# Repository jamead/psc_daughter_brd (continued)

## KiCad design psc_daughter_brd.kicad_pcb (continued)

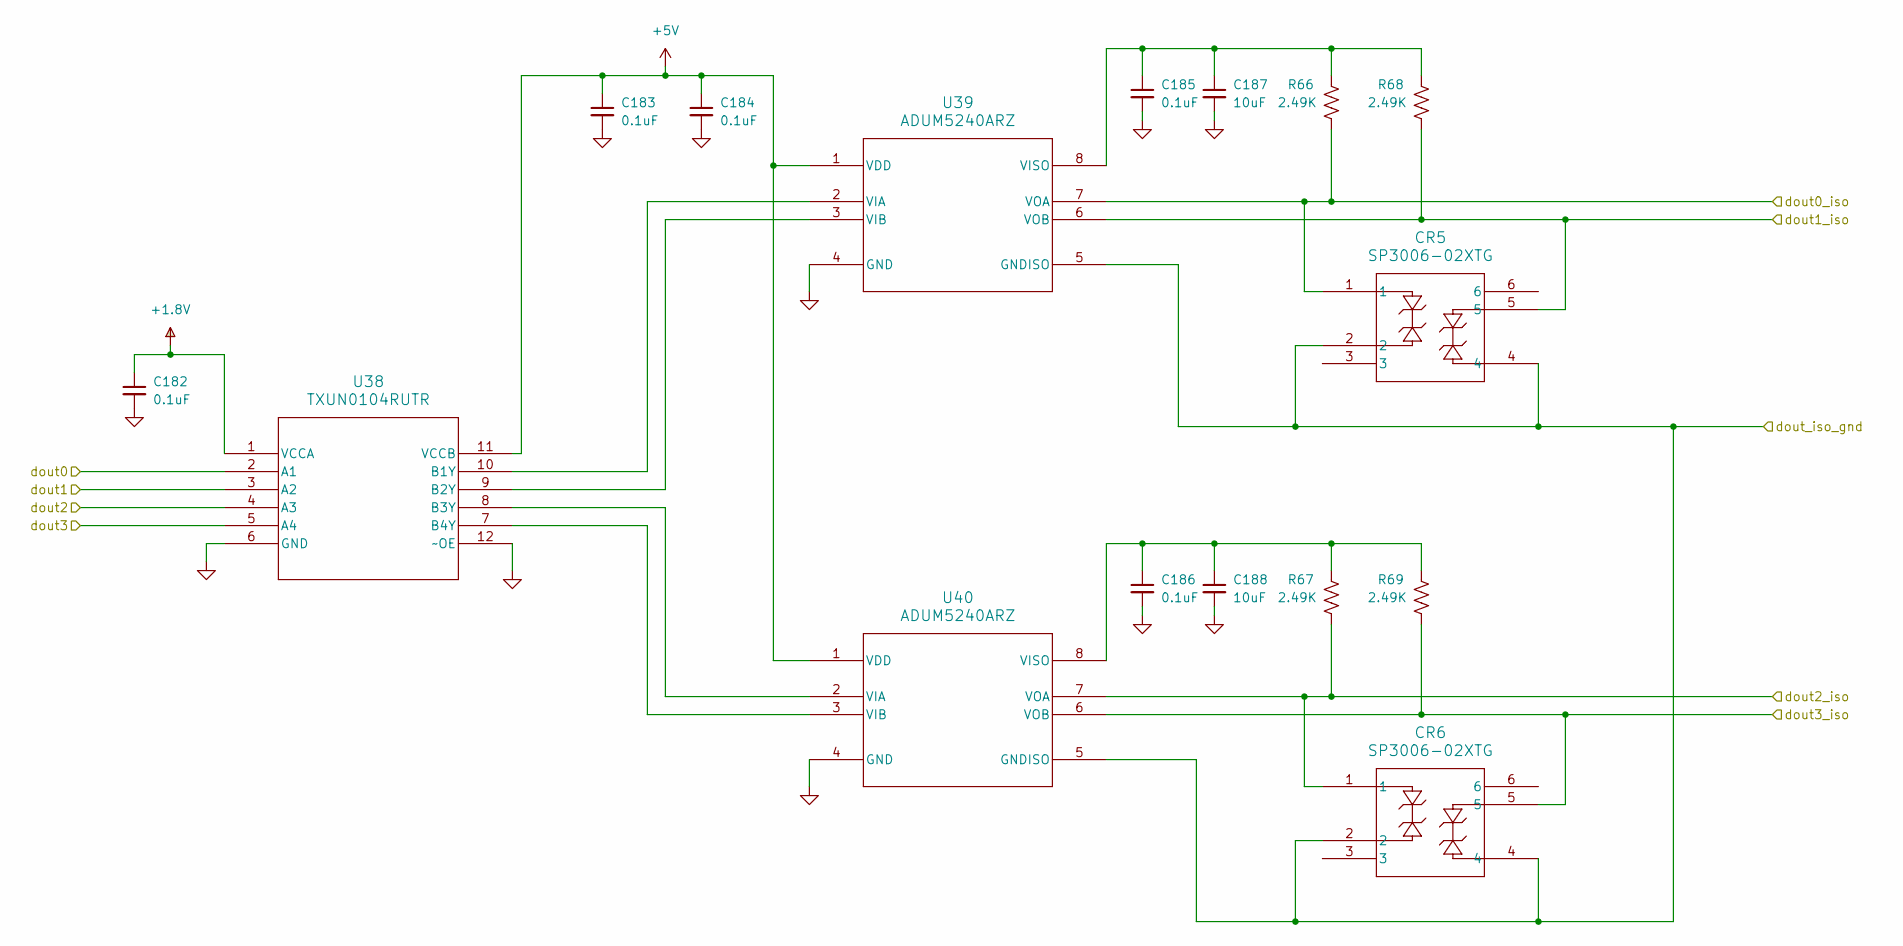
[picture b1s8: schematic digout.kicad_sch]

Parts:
C182, C183, C184, C185, C186: 0.1uF; C_0402_1005Metric
C187, C188: 10uF; C_0603_1608Metric; Voltage 25V
CR5, CR6: SP3006-02XTG; SOT563_LTF
R66, R67, R68, R69: 2.49K; R_0402_1005Metric; Tolerance 1%
U38: TXUN0104RUTR; PQFP12_RUT_TEX
U39, U40: ADUM5240ARZ; R_8_ADI

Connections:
+1.8V: C182.1, U38.1 (VCCA); also elsewhere on the board
+5V: C183.1, C184.1, U38.11 (VCCB), U39.1 (VDD), U40.1 (VDD); also elsewhere on the board
/FPGA connector/dout0: U38.2 (A1); also elsewhere on the board
/FPGA connector/dout1: U38.3 (A2); also elsewhere on the board
/FPGA connector/dout2: U38.4 (A3); also elsewhere on the board
/FPGA connector/dout3: U38.5 (A4); also elsewhere on the board
/Isolated Digital IO/dout0_iso: CR5.1, R66.1, U39.7 (VOA); also elsewhere on the board
/Isolated Digital IO/dout1_iso: CR5.5, R68.1, U39.6 (VOB); also elsewhere on the board
/Isolated Digital IO/dout2_iso: CR6.1, R67.1, U40.7 (VOA); also elsewhere on the board
/Isolated Digital IO/dout3_iso: CR6.5, R69.1, U40.6 (VOB); also elsewhere on the board
/Isolated Digital IO/dout_iso_gnd: CR5.2, CR5.4, CR6.2, CR6.4, U39.5 (GNDISO), U40.5 (GNDISO)
GND: C182.2, C183.2, C184.2, C185.2, C186.2, C187.2, C188.2, U38.6 (GND), U38.12 (~OE), U39.4 (GND), U40.4 (GND); also elsewhere on the board
unnamed: U38.10 (B1Y), U39.2 (VIA)
unnamed: U38.9 (B2Y), U39.3 (VIB)
unnamed: U38.8 (B3Y), U40.2 (VIA)
unnamed: U38.7 (B4Y), U40.3 (VIB)
unnamed: C185.1, C187.1, R66.2, R68.2, U39.8 (VISO)
unnamed: C186.1, C188.1, R67.2, R69.2, U40.8 (VISO)

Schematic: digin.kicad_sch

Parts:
C189, C190, C191, C192, C193: 0.1uF; C_0402_1005Metric
C194, C195: 10uF; C_0603_1608Metric; Voltage 25V
CR7, CR8: SP3006-02XTG; SOT563_LTF
R70, R71, R72, R73: 2.49K; R_0402_1005Metric; Tolerance 1%
U41: TXUN0104RUTR; PQFP12_RUT_TEX
U42, U43: ADUM5242ARZ; R_8_ADI

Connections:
+1V8: C189.1, U41.11 (VCCB)
+5V: C190.1, C191.1, U41.1 (VCCA), U42.1 (VDD), U43.1 (VDD); also elsewhere on the board
/FPGA connector/din0: U41.10 (B1Y); also elsewhere on the board
/FPGA connector/din1: U41.9 (B2Y); also elsewhere on the board
/FPGA connector/din2: U41.8 (B3Y); also elsewhere on the board
/FPGA connector/din3: U41.7 (B4Y); also elsewhere on the board
/Isolated Digital IO/din0_iso: CR7.1, R70.1, U42.7 (VIA); also elsewhere on the board
/Isolated Digital IO/din1_iso: CR7.5, R72.1, U42.6 (VIB); also elsewhere on the board
/Isolated Digital IO/din2_iso: CR8.1, R71.1, U43.7 (VIA); also elsewhere on the board
/Isolated Digital IO/din3_iso: CR8.5, R73.1, U43.6 (VIB); also elsewhere on the board
/Isolated Digital IO/din_iso_gnd: CR7.2, CR7.4, CR8.2, CR8.4, U42.5 (GNDISO), U43.5 (GNDISO)
GND: C189.2, C190.2, C191.2, C192.2, C193.2, C194.2, C195.2, U41.6 (GND), U41.12 (~OE), U42.4 (GND), U43.4 (GND); also elsewhere on the board
unnamed: U41.2 (A1), U42.2 (VOA)
unnamed: U41.3 (A2), U42.3 (VOB)
unnamed: U41.4 (A3), U43.2 (VOA)
unnamed: U41.5 (A4), U43.3 (VOB)
unnamed: C192.1, C194.1, R70.2, R72.2, U42.8 (VISO)
unnamed: C193.1, C195.1, R71.2, R73.2, U43.8 (VISO)

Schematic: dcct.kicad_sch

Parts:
C149, C150, C167, C169, C175, C177: 6800pF; C_0402_1005Metric
C151, C168, C176: 3300pF; C_0402_1005Metric
C152, C158, C163, C165, C173, C174, C179, C181: 0.1uF; C_0402_1005Metric
C154, C156, C161, C162, C171, C172, C178, C180: 10uF; C_0603_1608Metric; Voltage 25V
C159: 0.01uF; C_0402_1005Metric
R54, R55: 1.0K; R_0402_1005Metric; Tolerance 0.1%
R56: 665; R_0402_1005Metric; Tolerance 0.1%
R58: 1.3K; R_0402_1005Metric; Tolerance 1%
R62: 10; R_0402_1005Metric; Tolerance 0.1%
R63: 15; R_0402_1005Metric; Tolerance 0.1%
R64, R65: 30.1; R_0402_1005Metric; Tolerance 1%
U33: AD8429BRZ; SOIC127P600X175-8N
U34: AD8675ARZ; SOIC-8_3.9x4.9mm_P1.27mm
U36: LTC6363xMS8; MSOP-8_3x3mm_P0.65mm
U37: LTC2376CDE-20-PBF; DFN-16_DE_LIT

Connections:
+1.8V: C180.1, C181.1, U37.15 (OVDD); also elsewhere on the board
+2.5V: C178.1, C179.1, U37.2 (VDD); also elsewhere on the board
+5.3VA: C171.1, C173.1, U36.3 (V+); also elsewhere on the board
+15V: C156.1, C158.1, C162.1, C165.1, U33.8 (Vs+), U34.7 (V+); also elsewhere on the board
-5.3VA: C172.1, C174.1, U36.6 (V-); also elsewhere on the board
-15V: C152.1, C154.1, C161.1, C163.1, U33.5 (Vs-), U34.4 (V-); also elsewhere on the board
/DCCT ADCs/DCCT Channel 1/adc_vref: U37.7 (REF), U37.8 (REF/*DGC); also elsewhere on the board
/DCCT ADCs/DCCT Channel 1/drv_vref: U36.2 (VOCM); also elsewhere on the board
/DCCT ADCs/dcct0+: R55.2; also elsewhere on the board
/DCCT ADCs/dcct0-: R54.2; also elsewhere on the board
/DCCT ADCs/dcct0_sdo: U37.14 (SDO); also elsewhere on the board
/DCCT ADCs/dcct_busy: U37.11 (BUSY); also elsewhere on the board
/DCCT ADCs/dcct_cnv: U37.9 (CNV); also elsewhere on the board
/DCCT ADCs/dcct_sck: U37.13 (SCK); also elsewhere on the board
GND: C149.1, C150.2, C152.2, C154.2, C156.2, C158.2, C159.2, C161.2, C162.2, C163.2, C165.2, C167.1, C169.2, C171.2, C172.2, C173.2, C174.2, C175.1, C177.2, C178.2, C179.2, C180.2, C181.2, R63.2, U33.6 (Ref), U37.1 (CHAIN), U37.3 (GND), U37.6 (GND), U37.10 (GND), U37.12 (RDL/SDI), U37.16 (GND), U37.17 (GND); also elsewhere on the board
unnamed: C167.2, C168.1, R62.1, U36.8 (+)
unnamed: C168.2, C169.1, R63.1, U36.1 (-)
unnamed: R56.1, U33.2 (Rg)
unnamed: R56.2, U33.3 (Rg)
unnamed: R58.2, U33.7
unnamed: R64.2, U36.5 (-)
unnamed: R65.2, U36.4 (+)
unnamed: C150.1, C151.2, R55.1, U33.4 (+)
unnamed: C149.2, C151.1, R54.1, U33.1 (-)
unnamed: C159.1, R58.1, U34.3 (+)
unnamed: R62.2, U34.2 (-), U34.6
unnamed: C176.2, C177.1, R65.1, U37.4 (IN+)
unnamed: C175.2, C176.1, R64.1, U37.5 (IN-)

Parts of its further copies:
C114, C115, C132, C134, C140, C142: 6800pF; C_0402_1005Metric
C116, C133, C141: 3300pF; C_0402_1005Metric
C117, C123, C128, C130, C138, C139, C144, C146: 0.1uF; C_0402_1005Metric
C119, C121, C126, C127, C136, C137, C143, C145: 10uF; C_0603_1608Metric; Voltage 25V
C124: 0.01uF; C_0402_1005Metric
R42, R43: 1.0K; R_0402_1005Metric; Tolerance 0.1%
R44: 665; R_0402_1005Metric; Tolerance 0.1%
R46: 1.3K; R_0402_1005Metric; Tolerance 1%
R50: 10; R_0402_1005Metric; Tolerance 0.1%
R51: 15; R_0402_1005Metric; Tolerance 0.1%
R52, R53: 30.1; R_0402_1005Metric; Tolerance 1%
U27: AD8429BRZ; SOIC127P600X175-8N
U28: AD8675ARZ; SOIC-8_3.9x4.9mm_P1.27mm
U30: LTC6363xMS8; MSOP-8_3x3mm_P0.65mm
U31: LTC2376CDE-20-PBF; DFN-16_DE_LIT

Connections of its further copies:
+1.8V: C145.1, C146.1, U31.15 (OVDD); also elsewhere on the board
+2.5V: C143.1, C144.1, U31.2 (VDD); also elsewhere on the board
+5.3VA: C136.1, C138.1, U30.3 (V+); also elsewhere on the board
+15V: C121.1, C123.1, C127.1, C130.1, U27.8 (Vs+), U28.7 (V+); also elsewhere on the board
-5.3VA: C137.1, C139.1, U30.6 (V-); also elsewhere on the board
-15V: C117.1, C119.1, C126.1, C128.1, U27.5 (Vs-), U28.4 (V-); also elsewhere on the board
/DCCT ADCs/DCCT Channel 1/adc_vref: U31.7 (REF), U31.8 (REF/*DGC); also elsewhere on the board
/DCCT ADCs/DCCT Channel 1/drv_vref: U30.2 (VOCM); also elsewhere on the board
/DCCT ADCs/DCCT Channel 2/busy: U31.11 (BUSY)
/DCCT ADCs/dcct1+: R43.2; also elsewhere on the board
/DCCT ADCs/dcct1-: R42.2; also elsewhere on the board
/DCCT ADCs/dcct1_sdo: U31.14 (SDO); also elsewhere on the board
/DCCT ADCs/dcct_cnv: U31.9 (CNV); also elsewhere on the board
/DCCT ADCs/dcct_sck: U31.13 (SCK); also elsewhere on the board
GND: C114.1, C115.2, C117.2, C119.2, C121.2, C123.2, C124.2, C126.2, C127.2, C128.2, C130.2, C132.1, C134.2, C136.2, C137.2, C138.2, C139.2, C140.1, C142.2, C143.2, C144.2, C145.2, C146.2, R51.2, U27.6 (Ref), U31.1 (CHAIN), U31.3 (GND), U31.6 (GND), U31.10 (GND), U31.12 (RDL/SDI), U31.16 (GND), U31.17 (GND); also elsewhere on the board
unnamed: C132.2, C133.1, R50.1, U30.8 (+)
unnamed: C133.2, C134.1, R51.1, U30.1 (-)
unnamed: R44.1, U27.2 (Rg)
unnamed: R44.2, U27.3 (Rg)
unnamed: R46.2, U27.7
unnamed: R52.2, U30.5 (-)
unnamed: R53.2, U30.4 (+)
unnamed: C115.1, C116.2, R43.1, U27.4 (+)
unnamed: C114.2, C116.1, R42.1, U27.1 (-)
unnamed: C124.1, R46.1, U28.3 (+)
unnamed: R50.2, U28.2 (-), U28.6
unnamed: C141.2, C142.1, R53.1, U31.4 (IN+)
unnamed: C140.2, C141.1, R52.1, U31.5 (IN-)

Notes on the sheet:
Add TVS SP3118-01ETG
Replace with ADA4945-1

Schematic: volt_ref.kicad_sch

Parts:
C48, C52: 10uF; C_0603_1608Metric; Voltage 25V
C49, C50, C51: 0.1uF; C_0402_1005Metric
R11: 120; R_0402_1005Metric; Tolerance 1%
R12: 10; R_0402_1005Metric; Tolerance 1%
R13: DNP; R_0402_1005Metric; Tolerance 1%
R14: 79K; R_0402_1005Metric; Tolerance 1%
R15: 0; R_0402_1005Metric; Tolerance 1%
U12: ADR1001AEZ; E-20-1_ADI

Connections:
+15V: C48.1, C49.1, R15.2, U12.19 (VIN); also elsewhere on the board
/DAC/Voltage Reference/PWR_GOOD: U12.20 (PWRGD)
/DAC/Voltage Reference/REF_OUT: C50.1, C51.1, C52.1, U12.12 (BUF_F); also elsewhere on the board
GND: C48.2, C49.2, C51.2, C52.2, R11.1, R12.1, R13.1, U12.8 (INV1), U12.13 (BUF_GND), U12.14 (REF_GND), U12.15 (REF_GND), U12.16 (HTR_GND); also elsewhere on the board
unnamed: U12.10 (VDOUT), U12.11 (BUF_INP)
unnamed: C50.2, U12.7 (INV2), U12.9 (BUF_S)
unnamed: R12.2, U12.17 (HTR_ILIM)
unnamed: R15.1, U12.18 (HTR_IN)
unnamed: R11.2, U12.1 (ISET)
unnamed: R14.1, U12.4 (REF6P6_F), U12.5 (REF6P6_S), U12.6 (VDIN)
unnamed: R13.2, R14.2, U12.3 (TSET)

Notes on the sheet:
Configure TSET 40C: Short to REF6P6_F 60C: 79K to REF6P6_F 70C: Float Tset 90C: 63K to GND

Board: 10 copper layers, 278 parts (120 on the bottom side), 161 nets, no tracks yet.

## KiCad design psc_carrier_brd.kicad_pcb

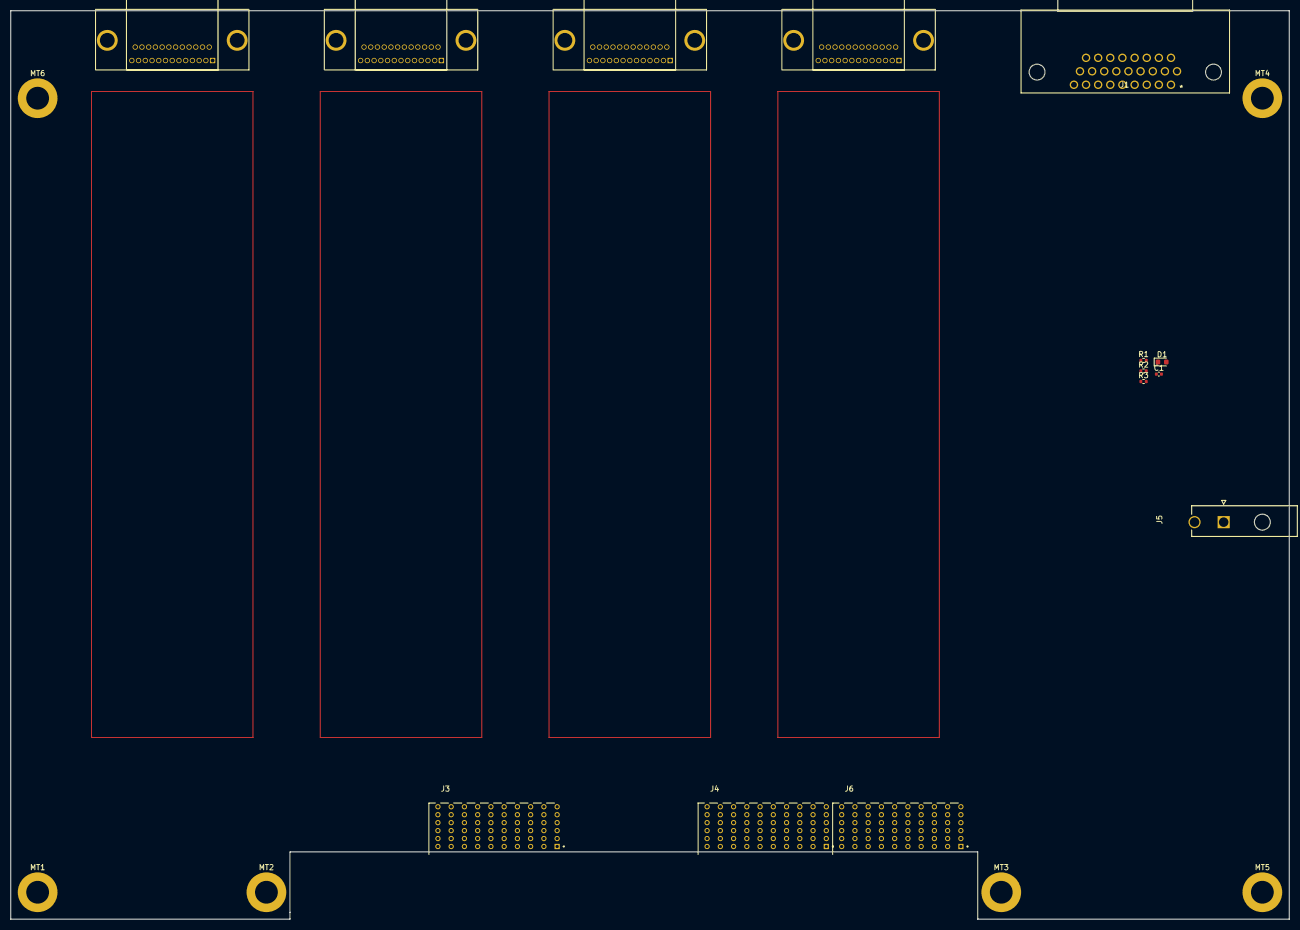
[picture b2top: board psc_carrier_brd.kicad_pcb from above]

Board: 2 copper layers, 241.3 x 171.4 mm, 20 parts (0 on the bottom side), 3 nets, no tracks yet.

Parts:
C1: C_Small; C_0402_1005Metric
D1: LED; LED_0603_1608Metric
J1: 1731130154; CONN_F15-26P135G0-5979_MOL
J2, J7, J8, J9: 0836149012
J3, J4, J6: 6469028-1; TE_6469028-1
J5: 39301022; MOLEX_39301022
MT1, MT2, MT3, MT4, MT5, MT6: MountingHole_Pad; MountingHole_4.3mm_M4_DIN965_Pad
R1: R_Small_US; R_0402_1005Metric
R2, R3: R_US; R_0402_1005Metric

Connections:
GND: C1.2, J3.BG1, J3.BG2, J3.BG3, J3.BG4, J3.BG5, J3.BG6, J3.BG7, J3.BG8, J3.BG9, J3.BG10, J3.DG1, J3.DG2, J3.DG3, J3.DG4, J3.DG5, J3.DG6, J3.DG7, J3.DG8, J3.DG9, J3.DG10, J4.BG1, J4.BG2, J4.BG3, J4.BG4, J4.BG5, J4.BG6, J4.BG7, J4.BG8, J4.BG9, J4.BG10, J4.DG1, J4.DG2, J4.DG3, J4.DG4, J4.DG5, J4.DG6, J4.DG7, J4.DG8, J4.DG9, J4.DG10, J6.BG1, J6.BG2, J6.BG3, J6.BG4, J6.BG5, J6.BG6, J6.BG7, J6.BG8, J6.BG9, J6.BG10, J6.DG1, J6.DG2, J6.DG3, J6.DG4, J6.DG5, J6.DG6, J6.DG7, J6.DG8, J6.DG9, J6.DG10, MT1.1, MT2.1, MT3.1, MT4.1, MT5.1, MT6.1
unnamed: C1.1, R1.2, R2.2, R3.2
unnamed: D1.1 (K), R1.1, R2.1, R3.1

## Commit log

2025-07-02 Initial commit, copied from Carrier Board
2025-07-02 Add DAC Sheet
2025-07-09 DAC section schematic updates
2025-07-13 Add ADR1001 Voltage Reference
2025-07-15 Add ADC monitor circuit
2025-11-17 Change board size, add DB connector
2025-11-18 Add isolated digital I/O
2025-11-20 Add DCCT ADCs
2025-11-22 DAC and DCCT placement
2025-11-24 finish rough placement
2025-12-01 Tweaks to connector pinouts
2025-12-03 Change DAC outputs to 1.8v
2026-01-05 Finish layout
2026-01-05 Add testpoints to BOM
2026-01-05 Rename BOM file
2026-01-05 Modify fab drawing
2026-01-06 Add drawing number
